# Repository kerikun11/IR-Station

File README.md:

# IR Station

Infrared Remote Controller with ESP8266 WiFi-module  
You can control your home appliances with your smartphone or laptop.

## Main parts

  * ESP-WROOM-02 (ESP8266 WiFi Module)
  * IR Receiver
  * IR LED
  * Indicator LED

## Looks

### The Device's Appearance

### Display Sample

## How to Use

see [How to Use IR-Station](how-to-use.md)

## How to Make

see [How to Make IR-Station](how-to-make.md)

## API References

see [API References of IR-Station](api-references.md)

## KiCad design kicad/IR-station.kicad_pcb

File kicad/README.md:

# IR-Station KiCad Project

- KiCad Version: 4

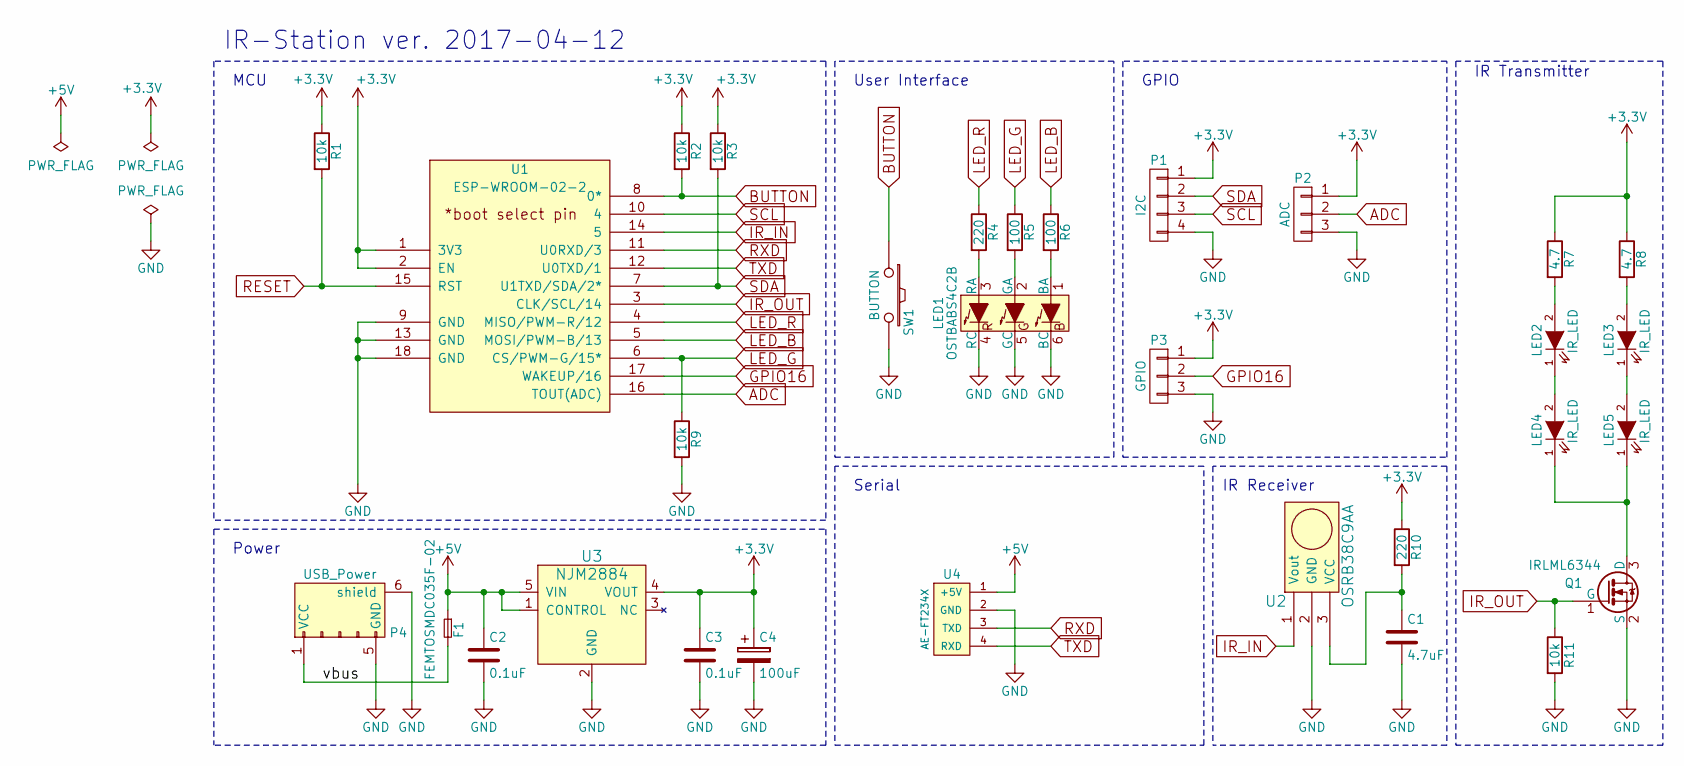
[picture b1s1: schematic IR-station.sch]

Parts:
C1: 4.7uF; C_0603
C2, C3: 0.1uF; C_0603
C4: 100uF; C_1206
F1: FEMTOSMDC035F-02; R_0603
LED1: OSTBABS4C2B
LED2, LED3, LED4, LED5: IR_LED; LED-3MM
P1: I2C; JST_SH_BM04B-SRSS-TB_04x1.00mm_Straight
P2: ADC; JST_SH_BM03B-SRSS-TB_03x1.00mm_Straight
P3: GPIO; JST_SH_BM03B-SRSS-TB_03x1.00mm_Straight
P4: USB_Power; USB_Micro_B_Power
Q1: IRLML6344; SOT-23
R1, R2, R3, R9, R11: 10k; R_0603
R4, R10: 220; R_0603
R5, R6: 100; R_0603
R7, R8: 4.7; R_2010
SW1: BUTTON; SW_PUSH
U1: ESP-WROOM-02-2; ESP-WROOM-02
U2: OSRB38C9AA; PL-IRMxxxx_Angle
U3: NJM2884; SOT89-5_Housing
U4: AE-FT234X; Pin_Header_Straight_1x04

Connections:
+3V3: C3.1, C4.1, P1.1, P2.1, P3.1, R1.1, R2.1, R3.1, R7.1, R8.1, R10.1, U1.1 (3V3), U1.2 (EN), U3.4 (VOUT)
+5V: C2.1, F1.1, U3.1 (CONTROL), U3.5 (VIN), U4.1 (+5V)
/vbus: F1.2, P4.1 (VCC)
ADC: P2.2, U1.16 (TOUT(ADC))
BUTTON: R2.2, SW1.1, U1.8 (0*)
GND: C1.2, C2.2, C3.2, C4.2, LED1.4 (RC), LED1.5 (GC), LED1.6 (BC), P1.4, P2.3, P3.3, P4.5 (GND), P4.6 (shield), Q1.2 (S), R9.2, R11.2, SW1.2, U1.9 (GND), U1.13 (GND), U1.18 (GND), U2.2 (GND), U3.2 (GND), U4.2 (GND)
GPIO16: P3.2, U1.17 (WAKEUP/16)
IR_IN: U1.14 (5), U2.1 (Vout)
IR_OUT: Q1.1 (G), R11.1, U1.3 (CLK/SCL/14)
LED_B: R6.1, U1.5 (MOSI/PWM-B/13)
LED_G: R5.1, R9.1, U1.6 (CS/PWM-G/15*)
LED_R: R4.1, U1.4 (MISO/PWM-R/12)
unnamed: C1.1, R10.2, U2.3 (VCC)
unnamed: LED1.1 (BA), R6.2
unnamed: LED1.2 (GA), R5.2
unnamed: LED1.3 (RA), R4.2
unnamed: LED2.1 (K), LED4.2 (A)
unnamed: LED2.2 (A), R7.2
unnamed: LED3.1 (K), LED5.2 (A)
unnamed: LED3.2 (A), R8.2
unnamed: LED4.1 (K), LED5.1 (K), Q1.3 (D)
RESET: R1.2, U1.15 (RST)
RXD: U1.11 (U0RXD/3), U4.3 (TXD)
SCL: P1.3, U1.10 (4)
SDA: P1.2, R3.2, U1.7 (U1TXD/SDA/2*)
TXD: U1.12 (U0TXD/1), U4.4 (RXD)

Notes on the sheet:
MCU
IR Receiver
IR Transmitter
Power
Serial
User Interface
GPIO
IR-Station ver. 2017-04-12

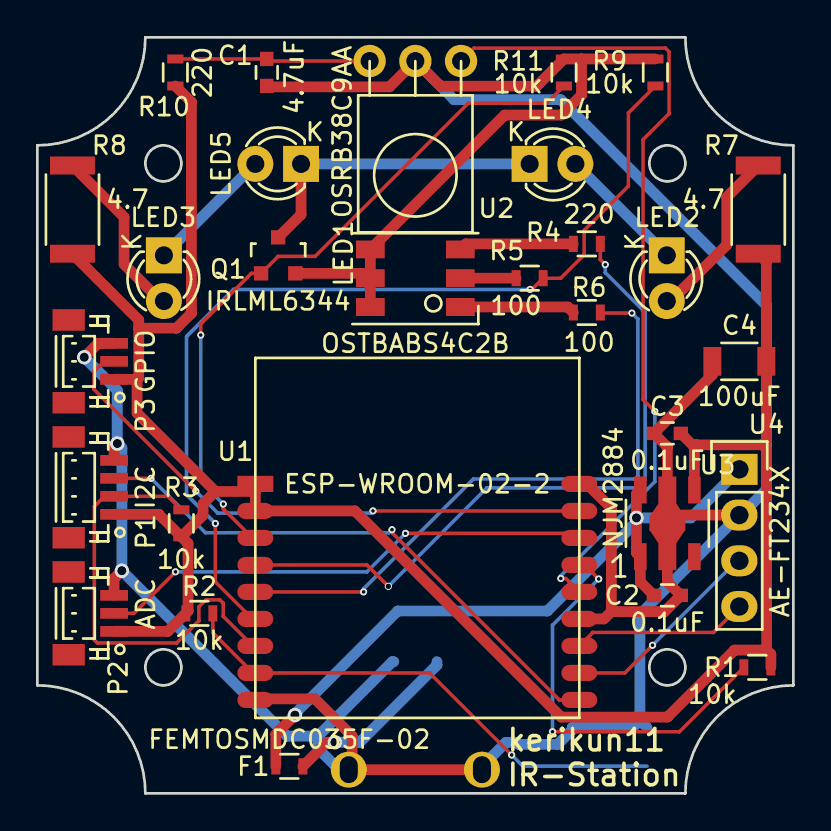
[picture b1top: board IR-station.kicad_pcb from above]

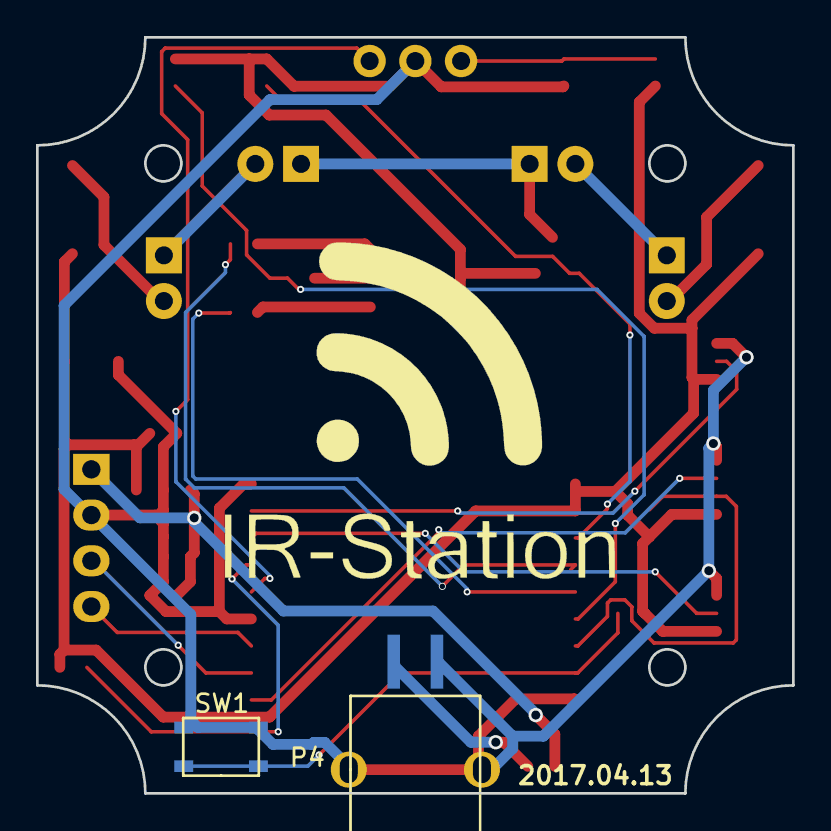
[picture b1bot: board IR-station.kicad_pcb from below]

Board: 2 copper layers, 42.0 x 42.0 mm, 31 parts (2 on the bottom side), 26 nets.

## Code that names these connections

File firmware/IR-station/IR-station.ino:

/*
  IR-station
  Infrared Remote Controller with ESP8266 WiFi Module

  Author:  kerikun11 (Github: kerikun11)
  Date:    2016.07.23

  The MIT License (MIT)
  Copyright (c)  2016  Ryotaro Onuki

  Permission is hereby granted, free of charge, to any person obtaining a copy of this software and associated documentation files (the "Software"), to deal in the Software without restriction, including without limitation the rights to use, copy, modify, merge, publish, distribute, sublicense, and/or sell copies of the Software, and to permit persons to whom the Software is furnished to do so, subject to the following conditions:
  The above copyright notice and this permission notice shall be included in all copies or substantial portions of the Software.
  THE SOFTWARE IS PROVIDED "AS IS", WITHOUT WARRANTY OF ANY KIND, EXPRESS OR IMPLIED, INCLUDING BUT NOT LIMITED TO THE WARRANTIES OF MERCHANTABILITY, FITNESS FOR A PARTICULAR PURPOSE AND NONINFRINGEMENT. IN NO EVENT SHALL THE AUTHORS OR COPYRIGHT HOLDERS BE LIABLE FOR ANY CLAIM, DAMAGES OR OTHER LIABILITY, WHETHER IN AN ACTION OF CONTRACT, TORT OR OTHERWISE, ARISING FROM, OUT OF OR IN CONNECTION WITH THE SOFTWARE OR THE USE OR OTHER DEALINGS IN THE SOFTWARE.
*/

#include <WiFi.h>
#include "config.h"
#include "station.h"

IR_Station *station;
volatile bool reset_flag = false;

void IRAM_ATTR rst_isr() {
  reset_flag = true;
}

void setup() {
  // prepare serial debug
  Serial.begin(115200);
  delay(10);
  println_dbg("");
  println_dbg("Hello, I'm ESP-WROOM-02");

  // IR-station setup
  station = new IR_Station(PIN_IR_OUT, PIN_IR_IN, PIN_LED_R, PIN_LED_G, PIN_LED_B);
  station->begin();

  // hardware button reset setup
  pinMode(PIN_BUTTON, INPUT_PULLUP);
  attachInterrupt(PIN_BUTTON, rst_isr, RISING);

  // Setup Completed
  println_dbg("Setup Completed");
}

void loop() {
  station->handle();
  if (reset_flag) station->reset();
}

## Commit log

2016-01-21 README.md
    Usage of IR-station
2016-01-21 firmware
    Arduino Firmware
2016-01-21 README.md
    small fix
2016-01-21 add serial debug
    Serial.print() を print_dbg() マクロに置き換え。
2016-01-22 edit debug
2016-01-22 README.md
    add how to make
2016-01-22 README.md
    how to make
2016-01-22 Circuit Diagram
    KiCad
2016-01-22 README.md
    table
2016-01-22 Change I/O Mapping
2016-01-22 LED
    Change LED color
2016-01-26 add comment
2016-01-26 add breadboard sample
2016-02-07 README
    small change
2016-02-11 Change IR recode system
    removed rawData
2016-02-11 Made IR Library
    IR Library can be used in general ways
2016-02-11 WDT bug fix
2016-02-12 Improved Program
    Easy to understand and debug
2016-02-12 Improve Server Program
    handleRoot()
    handleRequest()
    easy to understand
2016-02-15 move menu_buttons
2016-03-15 small change
    arduino board settings
    setup SSID
2016-03-17 JavaScriptで送受信
    static
    /
    JavaScript
    /send?id=1
    /recode?ch=2&chName=Light
    /settings?=clearAllSignals
2016-05-05 small change (JavaScript)
2016-05-05 ライブラリの依存関係を明確化
2016-05-10 SPIFFSサーバー化
    SPIFFSにhtmlやjsを置く．
2016-05-11 フォームを改良
    文字を大きくした．
    送信時に確認画面を出すようにした．
2016-05-11 WiFi接続の安定化
    WiFiのモードを適切に選択
2016-05-11 I2C接続LCDの導入
    IPアドレスを表示する．
2016-05-16 赤外線ライブラリの更新
    PWM機能を使って38kHzを作成
2016-05-20 リモコンデータをJson形式で保存に変更
    ArduinoJsonライブラリを使用．
    サンプルとしてで，ファイルシステムにリモコンデータを配置．
2016-05-25 安定性の向上
    ハードウェアボタンでWiFi切断ができるようになった．
    キャッシュされたWiFiに接続する前に，そのWiFiが存在するか確かめてから試みる．
2016-06-01 remove LCD and add Time
2016-06-01 remove global var target_ssid, target_pass
2016-06-01 small change: tpye
2016-06-19 PWM出力を廃止
    ちょうど38kHzにならないので，廃止．
2016-06-19 回路図を更新
2016-06-20 Update Breadboard Photo
2016-06-20 serveStatic()関数使用
    ファイルシステムからファイルを直に転送できる関数を使用
2016-06-20 デモ用のSinatraサーバーを追加
    ruby sinatraが必要
2016-06-20 Captive Portal 機能実装
    セットアップ時，APにつなぐと自動的にページが開く
2016-06-22 ブレッドボードの写真を更新
2016-06-22 modeSetupを変更
    様々な初期化処理をmodeSetupないで行う．
2016-06-22 バグ修正
    単純かつ致命的ミス
2016-06-22 ボタンによる初期化機能を再実装
    ピン変化割り込みによりWiFi切断(初期化)機能実装
2016-06-22 mDNS設定の更新
2016-06-22 MDNSが働かなくなる問題を修正
2016-06-22 依存関係の明確化
2016-06-22 初期化をmodeSetup()に統合
2016-06-22 mDNSがうまく働かない問題を修正
    原因は，OTAだった．
    試行錯誤の結果，OTAのセットアップをmDNSのセットアップの後にやってはいけないということがわかった．
2016-06-22 setup formのjavascriptにロード失敗時の処理を追加
    ロードに失敗したらメッセージを表示する．
2016-06-22 ファイルシステムのテキストデータをgzipで圧縮して転送を高速化
    高速化に伴い，ファイル階層を一部変更
2016-06-23 WiFi情報をファイルシステムにキャッシュするように設定
    SPIFFSのsettings.jsonにssidとpasswordを追加
2016-06-26 デバッグログを追加
2016-07-11 内容の更新
2016-07-11 Upload SPIFFSに参考URLを付加
2016-07-11 フルカラーLEDに対応
    インジケータLEDをフルカラーLEDに変更
2016-07-11 アイコンを1つにして軽量化
2016-07-23 ファイル名を一新，設定バックアップ文字列にcrc8機能
2016-07-23 Server-Demo
    README.mdを書いた．
    バグ修正.html->.htm
2016-07-23 KiCadデータを追加
    Ver. 1.0.1
2016-07-23 LEDインジケータの更新
2016-07-23 フォームの安定化
2016-07-23 内容の更新
    フルカラーLEDについての記述
2016-07-24 アイコンを中央寄せに．
2016-07-24 セットアップ方法の更新
    GET /confirm はSSIDなどを送信するだけで，すぐに接続を終わらせる．
    GET /isConnected に数秒ごとにアクセスして接続を確認する．
2016-07-24 WiFiが見つからなかった時の処理を追加
2016-07-24 安定化
    WiFi接続時にdelayを．
2016-07-24 ミスの修正
    書く場所を間違えた．
    機能には問題ない．
2016-07-25 回路図のトリミング
2016-07-25 IP通知機能を追加．
    ir.kerikeri.topからアクセスできるようになった．
2016-07-28 必ず受信失敗になってしまうバグ修正
2016-07-28 回路図とREADME.mdの更新
    FETにプルダウン抵抗
    部品表の更新
2016-07-29 ステルスSSIDも設定できるように変更
2016-07-29 サーバー名を変更
2016-07-29 セミコロンの付け忘れ解消
2016-08-03 mdns_hostnameをhostnameとして管理．
    mdnsを使わなくてもいいように徐々に移行
2016-08-10 いろいろ整理
2016-08-10 IRライブラリを変更
    ピン変化割り込みのライブラリを使用．
2016-08-11 APIを一新
    stealth-SSID用の接続
    Rename機能
    Clear機能
    Upload機能
2016-08-11 赤外線信号の追加
2016-08-13 JSONのダウンロード機能
    信号管理UIを更新
2016-08-13 JSONのダウンロード機能
    信号管理UIを更新
    HTML上ではチャンネル数が動的になった．name-listからチャンネル数を判定．
2016-08-13 画面の表示スタイルを変更
    より見やすく，操作しやすく．
2016-08-13 画面にインデントを．
2016-08-14 セットアップを改良 reboot API
2016-08-14 テスター用確認項目を作成
2016-08-14 表の修正
2016-08-14 製品一覧を追加
2016-08-14 ブラウザからファームウェアをアップデートする機能搭載
    /firmwareにアクセスする．
2016-08-18 Update Components and how to use
2016-08-18 HTTP APIを明記
2016-08-18 静的IPを使用
    mDNSのホスト名をurlからhostnameに変更
2016-08-18 静的IPを使用（続き）
2016-08-19 起動速度，安定性の向上
2016-08-19 READMEの更新
    不要な部分の削除
    JSONフォーマットの追加
    コードブロックの言語指定
2016-08-21 フォームの改良
2016-08-21 チャンネル数を増減可能に
    APIのみの実装．
    UIはまだ．
2016-08-22 チャンネル数を増減する機能
    UIを実装
2016-08-22 信号の登録のタイムアウトを延長
2016-08-24 READMEにチャンネル増減のAPIを追加
2016-08-25 回路図の更新
    発注基板のもの
2016-08-26 画像をディレクトリにまとめる
    画像が増えてきたのでディレクトリにまとめた．
    README.mdのパスも同時に変更．
2016-08-31 ブレッドボードサンプルの更新
    最新の回路図に合わせた構成
2016-09-08 固定IPの設定を実装(起動中のみ有効)
2016-09-08 static ipaddress, gw, netmaskをJSON形式で保存
2016-09-09 でもサーバーの更新
    IPアドレスの変更機能
2016-09-09 小さな修正
    HTMLのIDのform-sをform-submitに変更．
2016-09-14 recode -> record
    fix typo
2016-09-15 recode -> record
2016-09-16 基板の更新
    SHコネクタの使用
    AE-FT234Xの使用
    2016-09-16 発注済み
2016-09-21 static
    ir : static
2016-09-21 without button
2016-09-21 新API動作確認
    MITライセンスの導入
    とりあえず動くことを確認
    APモードは未確認
2016-09-21 READMEのAPIを更新
    新API
2016-09-22 READMEの小さな修正
2016-09-22 ハードウェアボタンでのリセットを実装
    mainでattach
2016-09-25 部品表を更新
    黄色プリント基板バージョン
2016-09-25 チャンネル数を変える機能
2016-09-25 メッセージの追加，名前の削除
    送信時にメッセージを表示
    clearしたときにname[ch]をクリア(するのを忘れていた)
2016-09-25 ヘッダーファイルの宣言の統一化
2016-09-25 応答メッセージを改良
    チャンネル名や番号を付加
2016-10-02 schedule機能の設計開始
    デモサーバーを実装
2016-10-02 disconnect()の修正
    チャンネル数を変えないように修正
2016-10-02 バージョンを表示する機能
2016-10-02 テスター資料の更新
2016-10-02 セットアップモードでのLEDの色を改良
    セットアップモードで自動的にWiFiに接続されたとき青だったのをシアンに変更
    状態をわかりやすくするため
2016-10-02 gzファイルの更新
2016-10-04 赤外線管理方法の変更(idの使用)
    固有な自然数idを割り当てる．
    row，column変数があるが，レイアウトは未実装．
2016-10-05 SPIFFSデータの更新
2016-10-05 CRC8を削除
    不要になったので削除
2016-10-05 IPアドレスの表示形式の修正
    IPアドレスの順番が逆だった．
    Informationは不可算名詞なので複数形のsを削除
2016-10-05 赤外線JSON形式の変更
    情報が生データだけになったので，JSONオブジェクトから，リスト形式に変更．
    将来は，バイナリデータにする予定である．
2016-10-05 Stringの文字数が長くても大丈夫なように修正
    もっと長くする必要があるかも．
    現状，50チャンネルは可能．
2016-10-07 時計ライブラリを追加
    NTPから時刻取得
2016-10-07 RAMを節約
    Stringに展開せずに逐次送信
2016-10-07 RAMの節約
    赤外線JSONを常に持たずに必要な時に生成
2016-10-07 デモサーバー側のスケジュール機能
    時間はUNIX時間で管理
2016-10-07 サーバーの誤字修正
    schedule -> schedules
2016-10-07 アクセスポイントにセキュリティキーを設置
    パスワードは IR-Station
2016-10-07 スケジュール機能追加によりバージョン更新
    v1.4.1 -> v1.5.0
2016-10-07 firmwareにスケジュールAPIを実装
    未動作確認
2016-10-08 スタックオーバーフローの修正
    JSON領域の動的確保に変更
2016-10-14 座標レイアウトを実装
    移動機能
2016-10-14 position構造体を解体
    なんかめんどくさくなった
2016-10-15 JSのaction振り分けにswitch文を使用
    より見やすく
2016-10-15 swpファイルの削除
2016-10-15 レイアウトの列数の制限を6に設定
2016-10-15 IPアドレスの固定のバグ修正
    Arduinoソースのミスにより固定不可だったのを修正
2016-10-15 デフォルトの赤外線信号を追加
    サンプルとして照明の赤外線信号を追加
2016-10-15 最新のAPIを記述
2016-10-16 デモサーバーにダウンロード用の赤外線データを保存
2016-10-16 サーバー公開用にconfig.ruを追加
    デモサーバーをApache2で公開するため．
2016-10-16 相対パスを絶対パスに修正
    公開サーバー用に相対にしたが，する必要はなかった．
2016-10-16 main.jsをより見やすく整理
2016-10-17 Actiionが成功したとき，警告を消す
2017-04-12 新しく基板を作成
    レギュレータを小型のものに変更
2017-04-15 基板にロゴを追加
2017-07-02 Scheduleのタイムゾーンのバグを修正
    UNIX時間で管理することで統一
2017-07-02 基板を4面でパネライズ
    実際に発注したデータ
2017-07-15 新基板用に部品表や画像を更新
2017-07-15 v1.5.1仕様に合わせてREADMEを更新
    新基板の写真も追加
2017-07-18 READMEを複数ファイルに分割
2017-07-18 誤字の修正
2017-09-12 リンク切れを修正
2018-12-17 READMEを更新 #11
2019-01-08 NTPサーバーアドレスを変更 #12
2019-04-21 バージョン情報を更新
2020-04-05 update documentations
2020-04-05 IR-station.ino,ir.h ISR not in IRAMに対する修正. https://community.platformio.org/t/how-to-fix-isr-not-in-iram/8031
2020-04-06 不要な記述の削除 #14
2020-04-06 自動フォーマットの適用
2020-04-06 記述を改良
2020-04-06 バージョンを更新 #14
2020-04-06 改行コードをUNIXスタイルに統一 #15
2020-04-07 バージョンが異なっても初期化しないように変更 #17
2020-04-07 バージョン情報を更新 #17
2020-04-07 READMEを更新
2020-04-11 OTA マクロで切り替え
2020-04-12 Alexa機能のテスト実装
2020-04-17 Gemfile sinatra
2020-04-17 ws.rb htmlテスト用webサーバー
2020-04-17 Alexa 追加のたたき台とUIのスクリプト修正
2020-04-18 selectのoptionのズレ修正
2020-04-18 main.js 複数シグナルセレクトボックスとUI初期化
2020-04-18 ws.rb UIデザイン円滑化のためのプロキシ
2020-04-18 不要ファイルのignore
2020-04-18 main.js Alexa post機能
2020-04-18 index.htm.erb Alexa追加のUI
2020-04-18 station.cpp AlexaデバイスをJSONに記録
2020-04-18 main.js AlexaデバイスのUI表示
2020-04-19 station.cpp Alexaからの指示実行と設定復元
2020-04-19 station.cpp Alexa指示で状態量も変更
2020-04-19 png,jquery,ico,tagsを除外
2020-04-19 date/ -> datetemplate/
2020-04-19 index.htm.erb -> main/
2020-04-19 Gemfile uglifier
2020-04-19 main.js style.css -> webUI/data/main/
2020-04-19 デプロイ機能
2020-04-19 webUI/.gitignore -> webUI/data/
2020-04-19 ignore /data/ to deploy
2020-04-19 スケジュールUIの変更
2020-04-19 webUI/README.adoc
2020-04-19 station.cpp Alexa状態量判定についてのメモ
2020-04-20 station.cpp Alexaの正常な追加と削除
2020-04-20 Alexa追加削除のUI一応完成
2020-04-23 ESP8266WebServerをAsyncWebServerに変更。SSDPは保留。httpUpdaterは廃止。displayRequest()でyieldが呼ばれるのは非同期だとまずい模様
2020-04-23 station.cpp safe_save()とAlexaデバイス登録確認。SSDPが悪さをしているのでコメントアウト
2020-04-23 IR-station.ino AlexaとWebServerの切り替えを無効化。ESP.reset()を実行するよう変更
2020-04-24 station.cpp startAlexa()とstopAlexa()を廃止
2020-04-24 SSDPをAsyncWebServerでも使えるように継承して改造
2020-09-27 デモサーバーの Dockerfile を追加
2020-12-18 PlatformIO に対応 #21
2020-12-18 update version
2020-12-18 fix typo
2020-12-19 WiFiのPSKをハッシュで保存する #23
2020-12-23 change board to ESP32 DevKit
2022-12-28 PSKの計算ミスを修正
2022-12-28 コードの改良のみ
2022-12-28 README.md と .clang-format の追加
2022-12-28 platformio.ini を改良
2022-12-28 コードを改良
2022-12-28 IPアドレスの更新方法を変更
2022-12-30 IRライブラリを汎用的に改良
2022-12-30 距離センサを追加
2022-12-30 センサーのピンを定義
2022-12-30 人感センサによる自動送信を追加
2023-01-02 パラメータを調整
2023-02-23 Git describe によるバージョン取得の対応
2023-02-23 パラメータ調整
2025-07-22 ファイル名WiFi.hの衝突回避
